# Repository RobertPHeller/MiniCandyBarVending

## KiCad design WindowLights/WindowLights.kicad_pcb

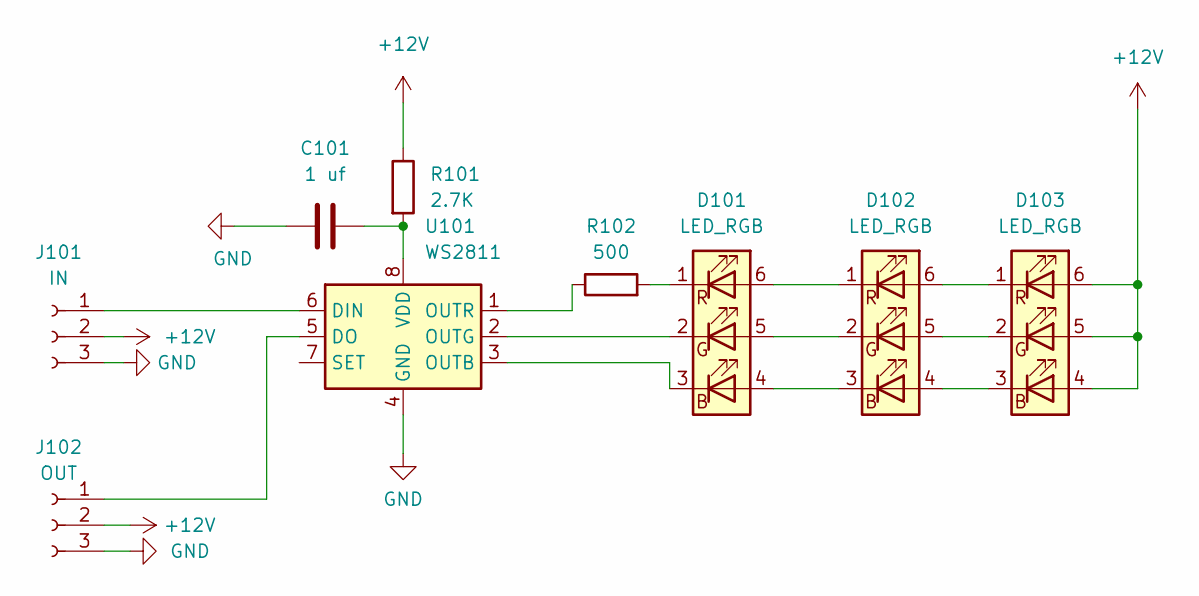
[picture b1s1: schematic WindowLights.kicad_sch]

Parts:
C101: 1 uf; C_0603_1608Metric; Mouser Part Number 963-MSASE168SC6105MT
D101, D102, D103: LED_RGB; LED_RGB_Cree-PLCC-6_6x5mm_P2.1mm; Mouser Part Number 941-P6CFKBCKNPRGJ7A3
J101: IN; JST_PH_S3B-PH-SM4-TB_1x03-1MP_P2.00mm_Horizontal; Mouser Part Number 306-S3BPHSM4TBLFSN
J102: OUT; JST_PH_S3B-PH-SM4-TB_1x03-1MP_P2.00mm_Horizontal; Mouser Part Number 306-S3BPHSM4TBLFSN
R101: 2.7K; R_0603_1608Metric; Mouser Part Number 667-ERA-3AED272V
R102: 500; R_0603_1608Metric; Mouser Part Number 603-RT0603BRC07500RL
U101: WS2811; SOP-8_3.9x4.9mm_P1.27mm; LCSC C114581

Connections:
+12V: D103.4 (BA), D103.5 (GA), D103.6 (RA), J101.2, J102.2, R101.1
GND: C101.1, J101.3, J102.3, U101.4 (GND)
unnamed: C101.2, R101.2, U101.8 (VDD)
unnamed: D101.1 (RK), R102.2
unnamed: D101.2 (GK), U101.2 (OUTG)
unnamed: D101.3 (BK), U101.3 (OUTB)
unnamed: D101.4 (BA), D102.3 (BK)
unnamed: D101.5 (GA), D102.2 (GK)
unnamed: D101.6 (RA), D102.1 (RK)
unnamed: D102.4 (BA), D103.3 (BK)
unnamed: D102.5 (GA), D103.2 (GK)
unnamed: D102.6 (RA), D103.1 (RK)
unnamed: J101.1, U101.6 (DIN)
unnamed: J102.1, U101.5 (DO)
unnamed: R102.1, U101.1 (OUTR)

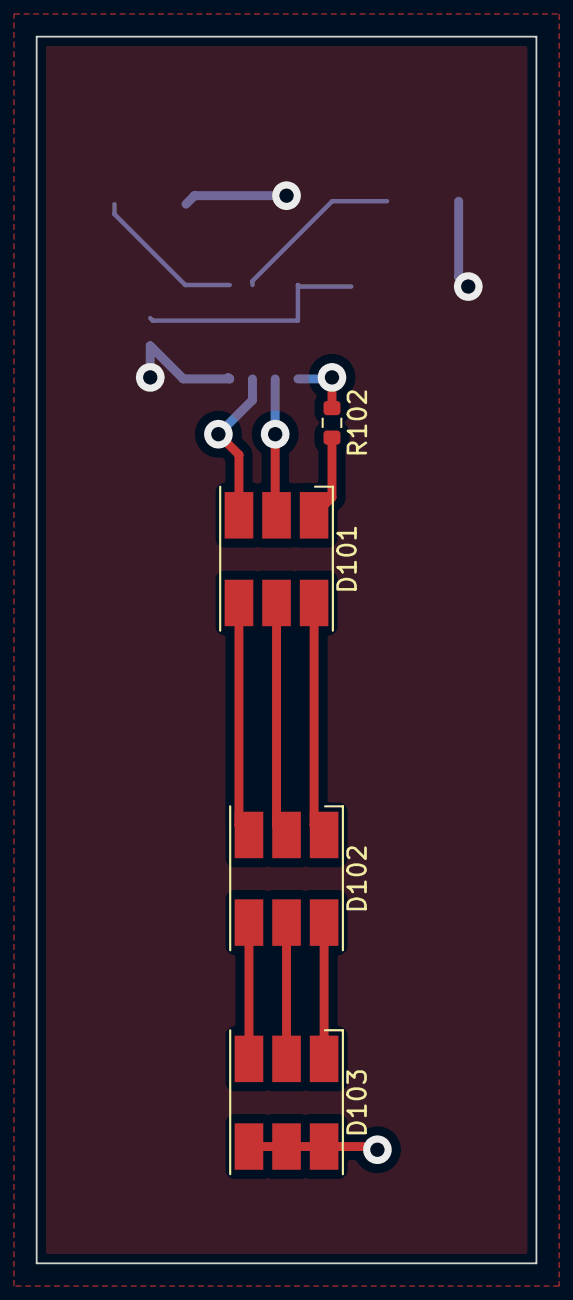
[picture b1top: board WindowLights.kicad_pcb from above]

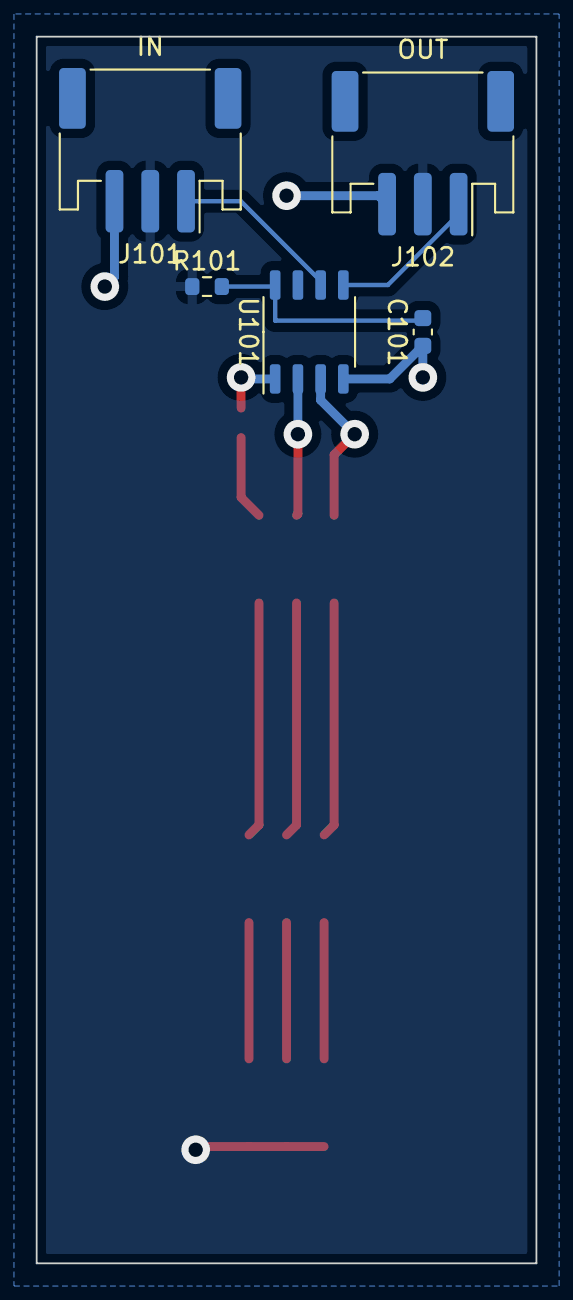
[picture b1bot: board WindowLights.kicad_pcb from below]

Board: 2 copper layers, 27.9 x 68.6 mm, 9 parts (5 on the bottom side), 15 nets.

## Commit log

2025-06-02 Transform matrix processing figured out! Update object names/labels.
2025-06-02 Add ViewFit.
2025-06-03 Update for new window sizes.
2025-06-03 Starting on creating FAB files.
2025-06-03 Working on creating FAB files.
2025-06-04 Trying mesh2solid coded from https://wiki.freecad.org/Mesh_to_Part.
2025-06-05 Latest test verson.
2025-06-06 Starting on panel version.
2025-06-07 Snapshot of panel version.
2025-06-08 Front part of entryway complete.
2025-06-09 Doors Started.
2025-06-09 Doors mostly completed (with hinges).
2025-06-09 Doors completed.
2025-06-09 Entryway light added and entryway completed.
2025-06-10 Tower Added.
2025-06-10 Bay Added.
2025-06-11 Left Wall Added.
2025-06-11 Right wall Added. Main house walls completed.
2025-06-13 Greenhouse started.
2025-06-13 Greenhouse started -- windows started.
2025-06-14 Greenhouse nearly done.
2025-06-14 Greenhouse windows done. Fixed minor bugs elsewhere.
2025-06-17 RoofSection class completed.
2025-06-17 Roof sections mostly done.
2025-06-20 Main roof sections done.
2025-06-20 Main roof sections done (final tweaks). Added back wall to tower.
2025-06-20 Main roof sections done (final tweaks).
2025-06-23 Tower roof done.
2025-06-23 Debug code commented out.
2025-06-23 Flat roof panels done.
2025-06-24 Completed greenhouse roof.
2025-06-25 Completed bay roof.
2025-06-28 Create InstanceIter ABC class.
2025-06-28 Most birch panels done (need to do roof and overhang sections).
2025-06-29 Added tower wraparound overhang ledge.
2025-06-29 Finished first draft of auto Panel Cut Pages.
2025-06-30 Cleaned up overlap errors.
2025-06-30 Added sorting.
2025-06-30 Nearly done -- smartened up BirchPanel.FitPanel() -- most (all?) cases handled.
2025-06-30 Additional tweaks.
2025-07-06 Start on Lurch pusher.
2025-07-07 Motor on its side.
2025-07-08 Add bottom and sides.
2025-07-08 Add Pillow Block and bearing.
2025-07-09 Tweak overall length.
2025-07-10 Completed basic pusher assembly.
2025-07-10 Add panel cutout sheets.
2025-07-11 Add limit switch mount.
2025-07-11 Add limit switches.
2025-07-11 Fine tune clearances.
2025-07-11 Tweaks to FitPanel to condense panel sheets.
2025-07-11 Start on Limit Switch Mount Block Drawing.
2025-07-12 Finish Limit Switch Mount Block Drawing.
